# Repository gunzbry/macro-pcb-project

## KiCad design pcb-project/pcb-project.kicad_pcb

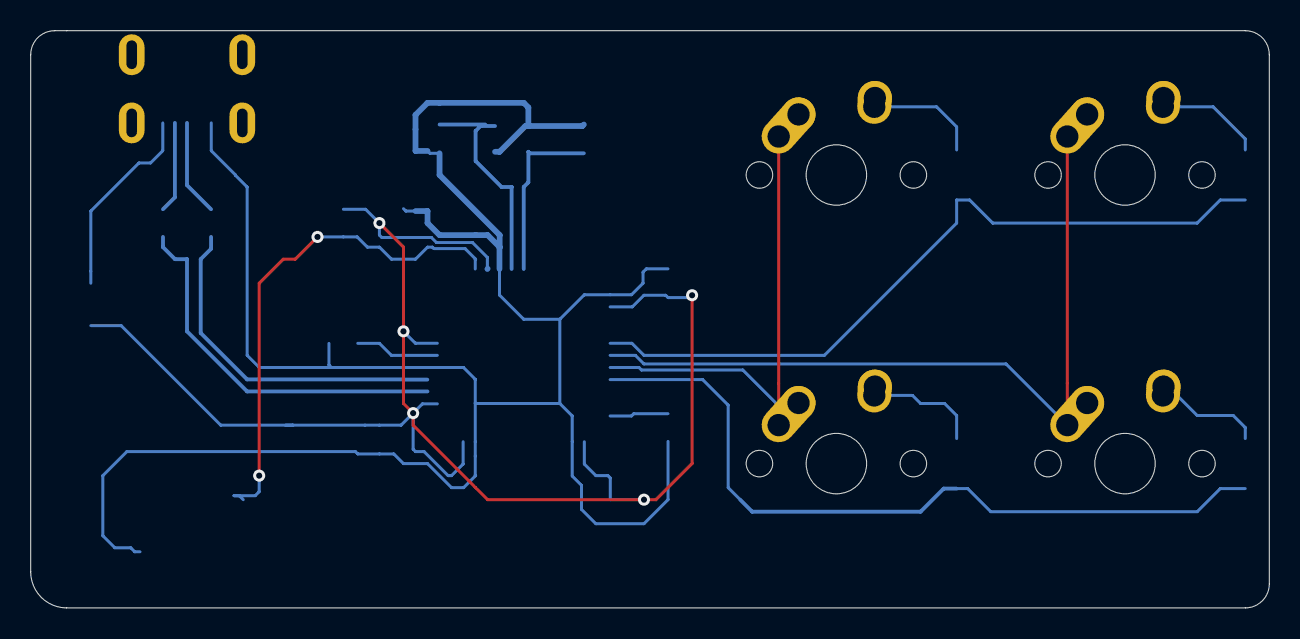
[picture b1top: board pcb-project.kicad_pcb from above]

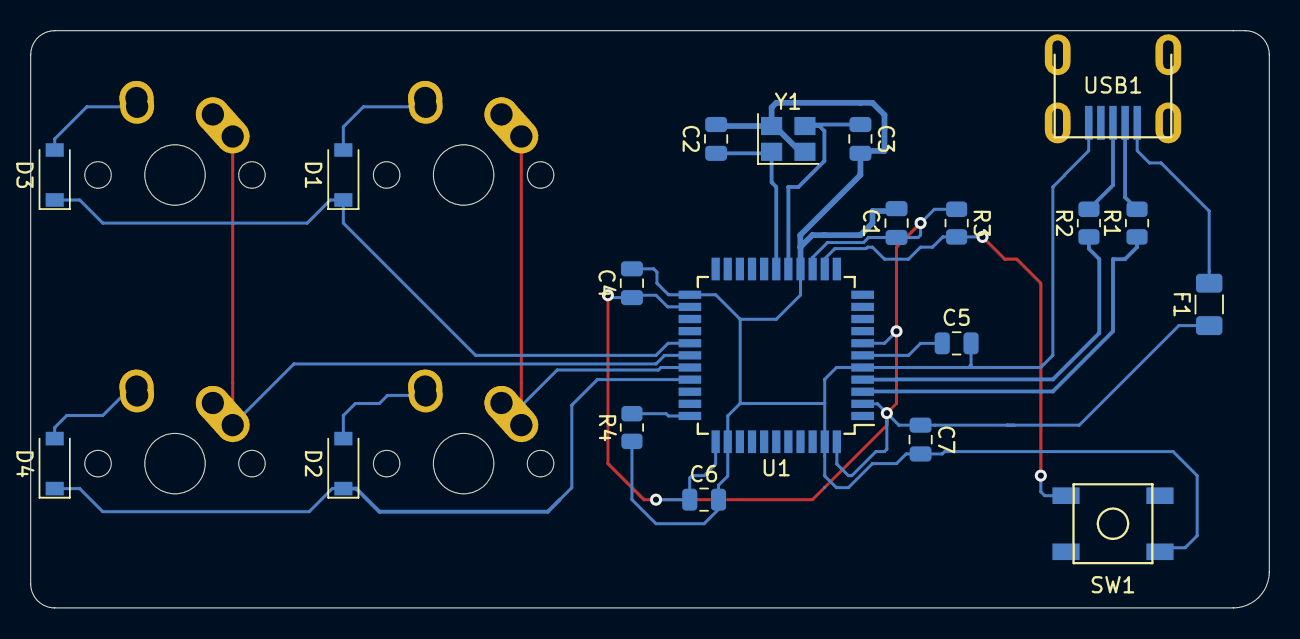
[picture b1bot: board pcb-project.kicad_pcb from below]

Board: 2 copper layers, 81.8 x 38.1 mm, 24 parts (20 on the bottom side), 20 nets.

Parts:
C1, C4, C6: 0.1uF; C_0805_2012Metric
C2, C3: 22pF; C_0805_2012Metric
C5: 1uF; C_0805_2012Metric
C7: 10uF; C_0805_2012Metric
D1, D2, D3, D4: S0D-123; D_SOD-123
F1: 500mA; Fuse_1206_3216Metric
MX1, MX2, MX3, MX4: MX-NoLED; MX-1U-NoLED
R1, R2: 22; R_0805_2012Metric
R3, R4: 10k; R_0805_2012Metric
SW1: SW_Push; SKQG-1155865
U1: ATmega32U4-A; TQFP-44_10x10mm_P0.8mm
USB1: Molex-0548190589
Y1: 16MHz; Crystal_SMD_3225-4Pin_3.2x2.5mm

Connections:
+5V: C1.1, C4.1, C6.1, C7.1, F1.1, R3.1, U1.2, U1.7, U1.14, U1.24, U1.34, U1.44
COL0: MX1.1, MX3.1, U1.29
COL1: MX2.1, MX4.1, U1.28
D+: R2.2, USB1.3
D-: R1.2, USB1.4
GND: C1.2, C2.2, C3.2, C4.2, C5.2, C6.2, C7.2, R4.1, SW1.1, U1.5, U1.15, U1.23, U1.35, U1.43, USB1.1, Y1.2, Y1.4
unnamed: C2.1, U1.17, Y1.1
unnamed: C3.1, U1.16, Y1.3
unnamed: C5.1, U1.6
unnamed: D1.2, MX1.2
unnamed: D2.2, MX3.2
unnamed: D3.2, MX2.2
unnamed: D4.2, MX4.2
unnamed: R1.1, U1.3
unnamed: R2.1, U1.4
unnamed: R3.2, SW1.2, U1.13
unnamed: R4.2, U1.33
ROW0: D1.1, D3.1, U1.27
ROW1: D2.1, D4.1, U1.30
VCC: F1.2, USB1.5

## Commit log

2021-05-05 Added submodules, mx_alpsHybrid, randomKeyboardParts
2021-05-05 fp-lib, and sym-lib configs
2021-05-05 fixed some configs
2021-05-05 added ATMega microchip symbols
2021-05-05 added tons of kicad libraries, drafted PCB
2021-05-05 PCB Routing
2021-05-05 generated gerber
2021-05-07 Added new RQM project
2021-05-07 RQM complete
